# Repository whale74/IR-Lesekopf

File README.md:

# IR-Lesekopf
KiCAD-Umsetzung des IR-Lesekopfs von volkszaehler.org (https://wiki.volkszaehler.org/hardware/controllers/ir-schreib-lesekopf-ttl-ausgang)
Darüber hinaus die Widerstände und Kondensatoren auf 0805 geändert, da ich diese standardmäßig nutze.
  
* Komponenten: https://www.reichelt.de/my/2109471 
* Gehäuse: https://www.thingiverse.com/thing:3378332
* Ringmagnet: https://www.amazon.de/gp/product/B00CL0IB08/

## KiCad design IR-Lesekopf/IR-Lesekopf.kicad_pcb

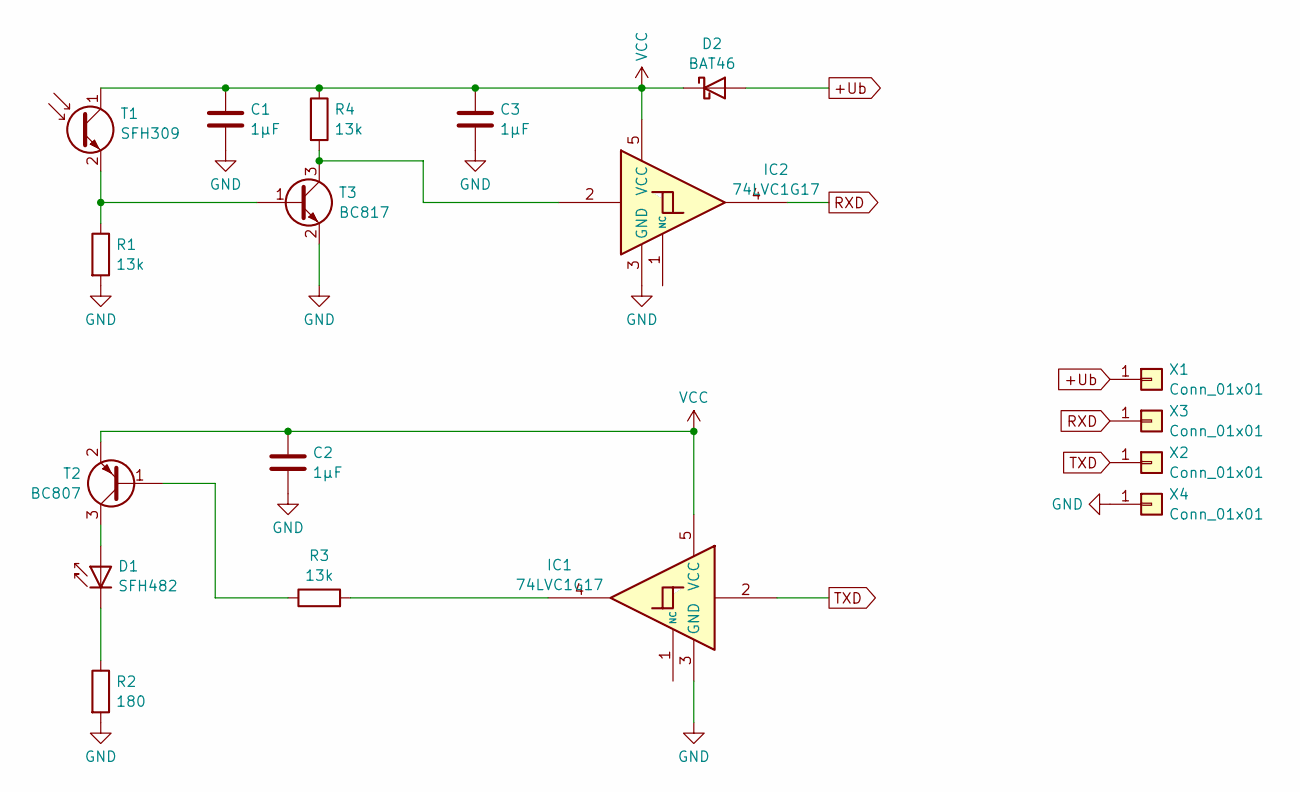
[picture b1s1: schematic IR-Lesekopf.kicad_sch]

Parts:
C1, C2, C3: 1µF; C_0805_2012Metric_Pad1.18x1.45mm_HandSolder
D1: SFH482; LED_D3.0mm_Clear
D2: BAT46; D_SOD-123
IC1, IC2: 74LVC1G17; SOT-23-5_HandSoldering
R1, R3, R4: 13k; R_0805_2012Metric_Pad1.20x1.40mm_HandSolder
R2: 180; R_0805_2012Metric_Pad1.20x1.40mm_HandSolder
T1: SFH309; LED_D3.0mm_Clear
T2: BC807; SOT-23
T3: BC817; SOT-23
X1, X2, X3, X4: Conn_01x01; SolderWirePad_1x01_SMD_2x3.5mm

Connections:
+Ub: D2.2 (A), X1.1
GND: C1.2, C2.2, C3.2, IC1.3 (GND), IC2.3 (GND), R1.2, R2.2, T3.2 (E), X4.1
unnamed: D1.2 (A), T2.3 (C)
unnamed: D1.1 (K), R2.1
unnamed: IC1.4, R3.2
unnamed: R1.1, T1.2 (E), T3.1 (B)
unnamed: R3.1, T2.1 (B)
unnamed: IC2.2, R4.2, T3.3 (C)
RXD: IC2.4, X3.1
TXD: IC1.2, X2.1
VCC: C1.1, C2.1, C3.1, D2.1 (K), IC1.5 (VCC), IC2.5 (VCC), R4.1, T1.1 (C), T2.2 (E)

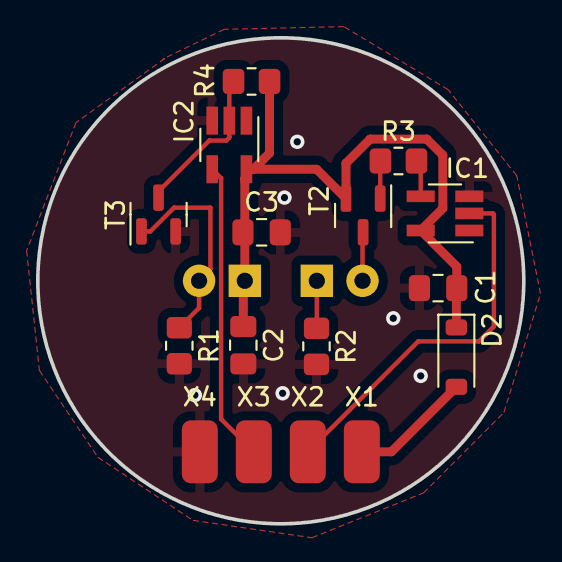
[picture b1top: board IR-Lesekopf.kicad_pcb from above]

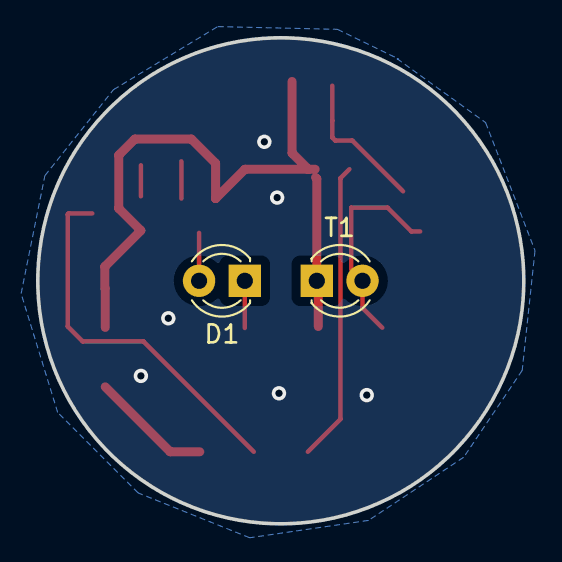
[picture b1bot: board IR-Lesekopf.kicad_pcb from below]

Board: 2 copper layers, 27.0 x 27.0 mm, 18 parts (2 on the bottom side), 11 nets.
